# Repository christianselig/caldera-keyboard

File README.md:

# ⌨️ Caldera Keyboard

This repo contains:

- The [Ergogen](https://github.com/ergogen/ergogen) v4 `config.yaml` file
- The outputted PCB files for use in KiCad (both the wired and uncompleted versions) available in the `ergogen` directory
- The left key plate JSCAD file generated by Ergogen (as well as the converted STL version). Note that no right side is included as in Fusion 360 I simply build out the case using the left side and then mirror the case with some modifications
- The ZMK firmware files for Caldera
- The completed case files for 3D printing can be found here: https://makerworld.com/en/models/545431

## Video

A full overview of the build process for this keyboard can be found on YouTube here: https://www.youtube.com/watch?v=7UXsD7nSfDY

## Instructions

If you're interested in building a Caldera keyboard, you can use the left and right `gerber.zip` files in this directory and upload those to a PCB manufacturer like JLCPCB or PCBWay (neither are sponsors) to obtain the PCBs. Then it's just a matter of acquiring the other keyboard parts from a site like Typeractive, and following the steps in the video above (soldering, assembling, flashing firmware).

Otherwise hopefully you can use some of these files and instructions as a jumping off point for building your own cool custom keyboard!

# Ergogen config.yaml overview

The Ergogen `config.yaml` file used for this keyboard is expanded upon versus the overview in the YouTube video above, and while there's comments throughout the file to help, I wanted to give a somewhat more substantial overview of how the file works.

## Mirror strategy

One important point is that when building a PCB for split keyboards, many people build a reversible PCB so that the same PCB can be used for both the left and right side, the benefits being you're only maintaining one PCB and when ordering PCBs from manufacturers (which often have a minimum order size of 5), you can just order the 5, rather than using a separate PCB for the left and right side and needing to order 5 of *each*, which can feel excessive.

All that to say, Caldera does *not* use a reversible PCB. 😄 Why? 

- I'm just learning Ergogen and KiCad, making the PCB reversible seemed like it added a lot of complexity that wasn't immediately clear to me, so this feels a bit more beginner friendly
- Since Caldera stashes the controller underneath the actual keys (unlike most keyboards which have it separated in its own area), it was quite challenging to maneuver all the controller pins/holes so they wouldn't run into keys/diodes/etc., making the PCB reversible would have made an already difficult task much more so
- Most of the cost in ordering PCBs is the shipping, so ordering 5 PCBs versus 10 PCBs isn't a big deal, if anything it's just more PCBs to have in case you mess something up somehow

This is accomplished through Ergogen's `mirror_` suffix which allows you to create a mirrored image of a specific component. However both sides of the keyboard still maintain the same controller pin locations, and are simply horizontally mirrored.

## Outlines

There may be simpler ways to define the outlines of the PCB, but I elected to define the points (like the anchor point tool in Figma/Sketch/Illustrator) for more control.

## Component positioning

The Ergogen config uses a lot of custom positioning to allow for the controller to fit underneath the board properly or around mounting holes, which can make routing traces a bit trickier but still totally possible. 

For instance diodes aren't uniformly placed, you can see this in the `config.yaml` where I use regex extensively to apply positioning to only specific diodes, for example whether or not they start with `mirror_` or start with `matrix_`, which dictates which side of the board they're on. I also use regex to target specific rows or columns.

## KiCad

Ergogen outputs PCBs to be wired up in KiCad, which is a relatively simple and honestly kinda fun task. Note that you sometimes end up with `.kicad_proj` files, and you can safely ignore those and just use the `.kicad_pcb` files directly.

One area I didn't touch on in the video was the concept of Vias. Remember, you have two sides of your PCB (in KiCad, the red side, and the blue side), which you can use to your routing advantage. When routing traces in KiCad, sometimes you'll hit a situation where you need to run a trace but another trace is in the way of your path. Sometimes the best way to solve this is to use a Via, which just creates a hole in the PCB to the other side so you can safely route your trace on the other side where there hopefully isn't also something in the way, and if need be, you can Via back to the other side to finish the trace. Very handy, but try not to abuse it too much versus just being smart with your routing (I use it probably a bit more than I should as a beginner, but it's not the end of the world).

A warning you might receive in KiCad when routing the Ergogen schematic is: `Warning: The current configuration does not include the library ''.` From all I can gather, this is just a bug that has no meaningful effect, and you can safely ignore it. There's also a bunch of warnings for `Warning: Silkscreen clipped by solder mask`, this one I don't fully understand (my understanding is the silkscreen is *on top* of the solder mask, so not sure how that's possible), but it's only a warning, not an error, so it's not something I've had any issue ignoring. From what I gather it *might* refer to the silkscreen being cut out by holes in the solder mask/PCB, but again, we're just using the silkscreen as labels, so not to worry if that is the case.

However you do always want to run the Design Rules Checker (DRC aka The Validator) to see if you have any actual errors, and can also help you find which traces are unrouted.

## Cases

I use the handy Ergogen `cases` feature to easily use the key positioning to generate a 3D model file for the plate that the key switches click into, which is much nicer than manually doing everything in CAD software (which I use after Ergogen did a bunch of the heavy lifting). And yeah a 3D printed key plate in PLA is more than strong enough.

## Nothin' fancy

There are changes you could make to this PCB design to make it better, but I did not do:

- Change track width in KiCad. This would give you more resilient, sturdier traces for the electricity to pass through, but I just used the thinner KiCad default. Easier to route and honestly for keyboards and the tiny amount of electricity flowing it really feels negligible, but you can always re-trace the PCB yourself in KiCad with thicker traces!
- Reversible PCB: I did not do this, see *Mirror strategy* for why
- Ground plane: some folks build a ground plane into the PCB rather than requiring wiring directly to a ground pin. I'm not going to lie, I don't 100% understand this, it confused me, and from what I read seemed also negligible for keyboard PCBs, but would be a fun extra thing to learn!

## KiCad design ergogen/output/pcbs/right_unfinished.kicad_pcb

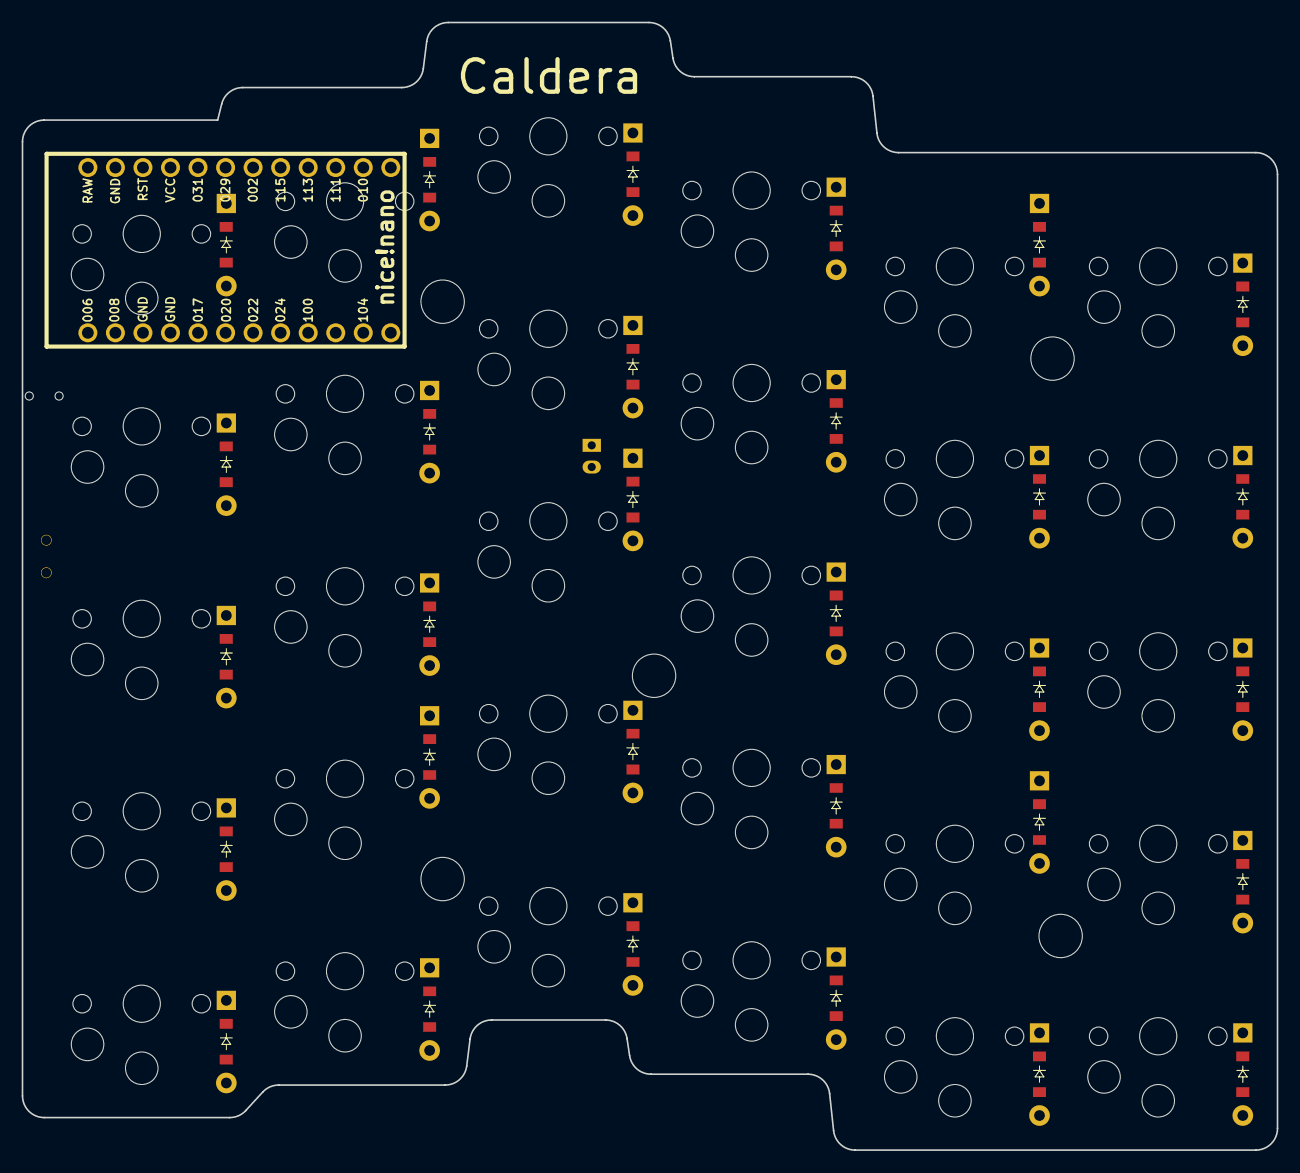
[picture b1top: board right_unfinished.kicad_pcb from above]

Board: 2 copper layers, 115.8 x 104.0 mm, 64 parts (0 on the bottom side), 45 nets, no tracks yet.

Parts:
B1: Panasonic_EVQPUL_EVQPUC
D1, D2, D3, D4, D5, D6, D7, D8, D9, D10, D11, D12, D13, D14, D15, D16, D17, D18, D19, D20, D21, D22, D23, D24, D25, D26, D27, D28, D29, D30: ComboDiode
JST1: JST_PH_S2B-PH-K_02x2.00mm_Angled
MCU1: nice_nano
S1, S2, S3, S4, S5, S6, S7, S8, S9, S10, S11, S12, S13, S14, S15, S16, S17, S18, S19, S20, S21, S22, S23, S24, S25, S26, S27, S28, S29, S30: PG1350
T1: SPDT_C128955

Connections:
GND: B1.1, JST1.2, MCU1.3, MCU1.4, MCU1.23
P002: D3.1, D7.1, D11.1, D19.1, D23.1, D27.1, MCU1.18
P011: MCU1.10, S21.1, S22.1, S23.1, S24.1, S25.1
P017: MCU1.5, S26.1, S27.1, S28.1, S29.1, S30.1
P020: MCU1.6, S1.1, S2.1, S3.1, S4.1, S5.1
P022: MCU1.7, S6.1, S7.1, S8.1, S9.1, S10.1
P024: MCU1.8, S11.1, S12.1, S13.1, S14.1, S15.1
P029: D4.1, D8.1, D12.1, D16.1, D20.1, D24.1, MCU1.19
P031: D5.1, D13.1, D17.1, D26.1, D29.1, D30.1, MCU1.20
P100: MCU1.9, S16.1, S17.1, S18.1, S19.1, S20.1
P113: D1.1, D6.1, D9.1, D14.1, D18.1, D21.1, MCU1.16
P115: D2.1, D10.1, D15.1, D22.1, D25.1, D28.1, MCU1.17
RAW: MCU1.24, T1.2
RST: B1.2, MCU1.22
mirror_fifth_bottom: D28.2, S22.2
mirror_fifth_home: D19.2, S23.2
mirror_fifth_mod: D18.2, S21.2
mirror_fifth_num: D29.2, S25.2
mirror_fifth_top: D20.2, S24.2
mirror_first_bottom: D2.2, S2.2
mirror_first_home: D3.2, S3.2
mirror_first_mod: D1.2, S1.2
mirror_first_num: D5.2, S5.2
mirror_first_top: D4.2, S4.2
mirror_fourth_bottom: D15.2, S17.2
mirror_fourth_home: D27.2, S18.2
mirror_fourth_mod: D14.2, S16.2
mirror_fourth_num: D17.2, S20.2
mirror_fourth_top: D16.2, S19.2
mirror_second_bottom: D25.2, S7.2
mirror_second_home: D7.2, S8.2
mirror_second_mod: D6.2, S6.2
mirror_second_num: D26.2, S10.2
mirror_second_top: D8.2, S9.2
mirror_sixth_bottom: D22.2, S27.2
mirror_sixth_home: D23.2, S28.2
mirror_sixth_mod: D21.2, S26.2
mirror_sixth_num: D30.2, S30.2
mirror_sixth_top: D24.2, S29.2
mirror_third_bottom: D10.2, S12.2
mirror_third_home: D11.2, S13.2
mirror_third_mod: D9.2, S11.2
mirror_third_num: D13.2, S15.2
mirror_third_top: D12.2, S14.2
pos: JST1.1, T1.1

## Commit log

2023-11-14 Initial PCB prototype
2024-07-18 Add main files
2024-07-18 Modify README
2024-07-18 Add missing KiCad files
2024-08-30 add the required zmk config for deep sleep wake
2024-08-31 add support for keymap editor
